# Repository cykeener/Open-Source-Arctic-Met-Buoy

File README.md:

# Open-Source-Arctic-Met-Buoy
General info, PCB design files, and hull / enclosure design files to build a meteorological (met) buoy to collect GPS location, external temperature, and atmospheric pressure in a cold weather environment.  This version of the buoy was designed in the fall of 2018, and deployed in the winter of 2019.

The intent of this repository is to maintain general info, PCB design files (from Eagle), 3D printable stl files (from Fusion 360), and a series of BOMs that will allow the user to build an open source met buoy that runs on Arduino code maintained by tgidave https://github.com/tgidave/icedrifter

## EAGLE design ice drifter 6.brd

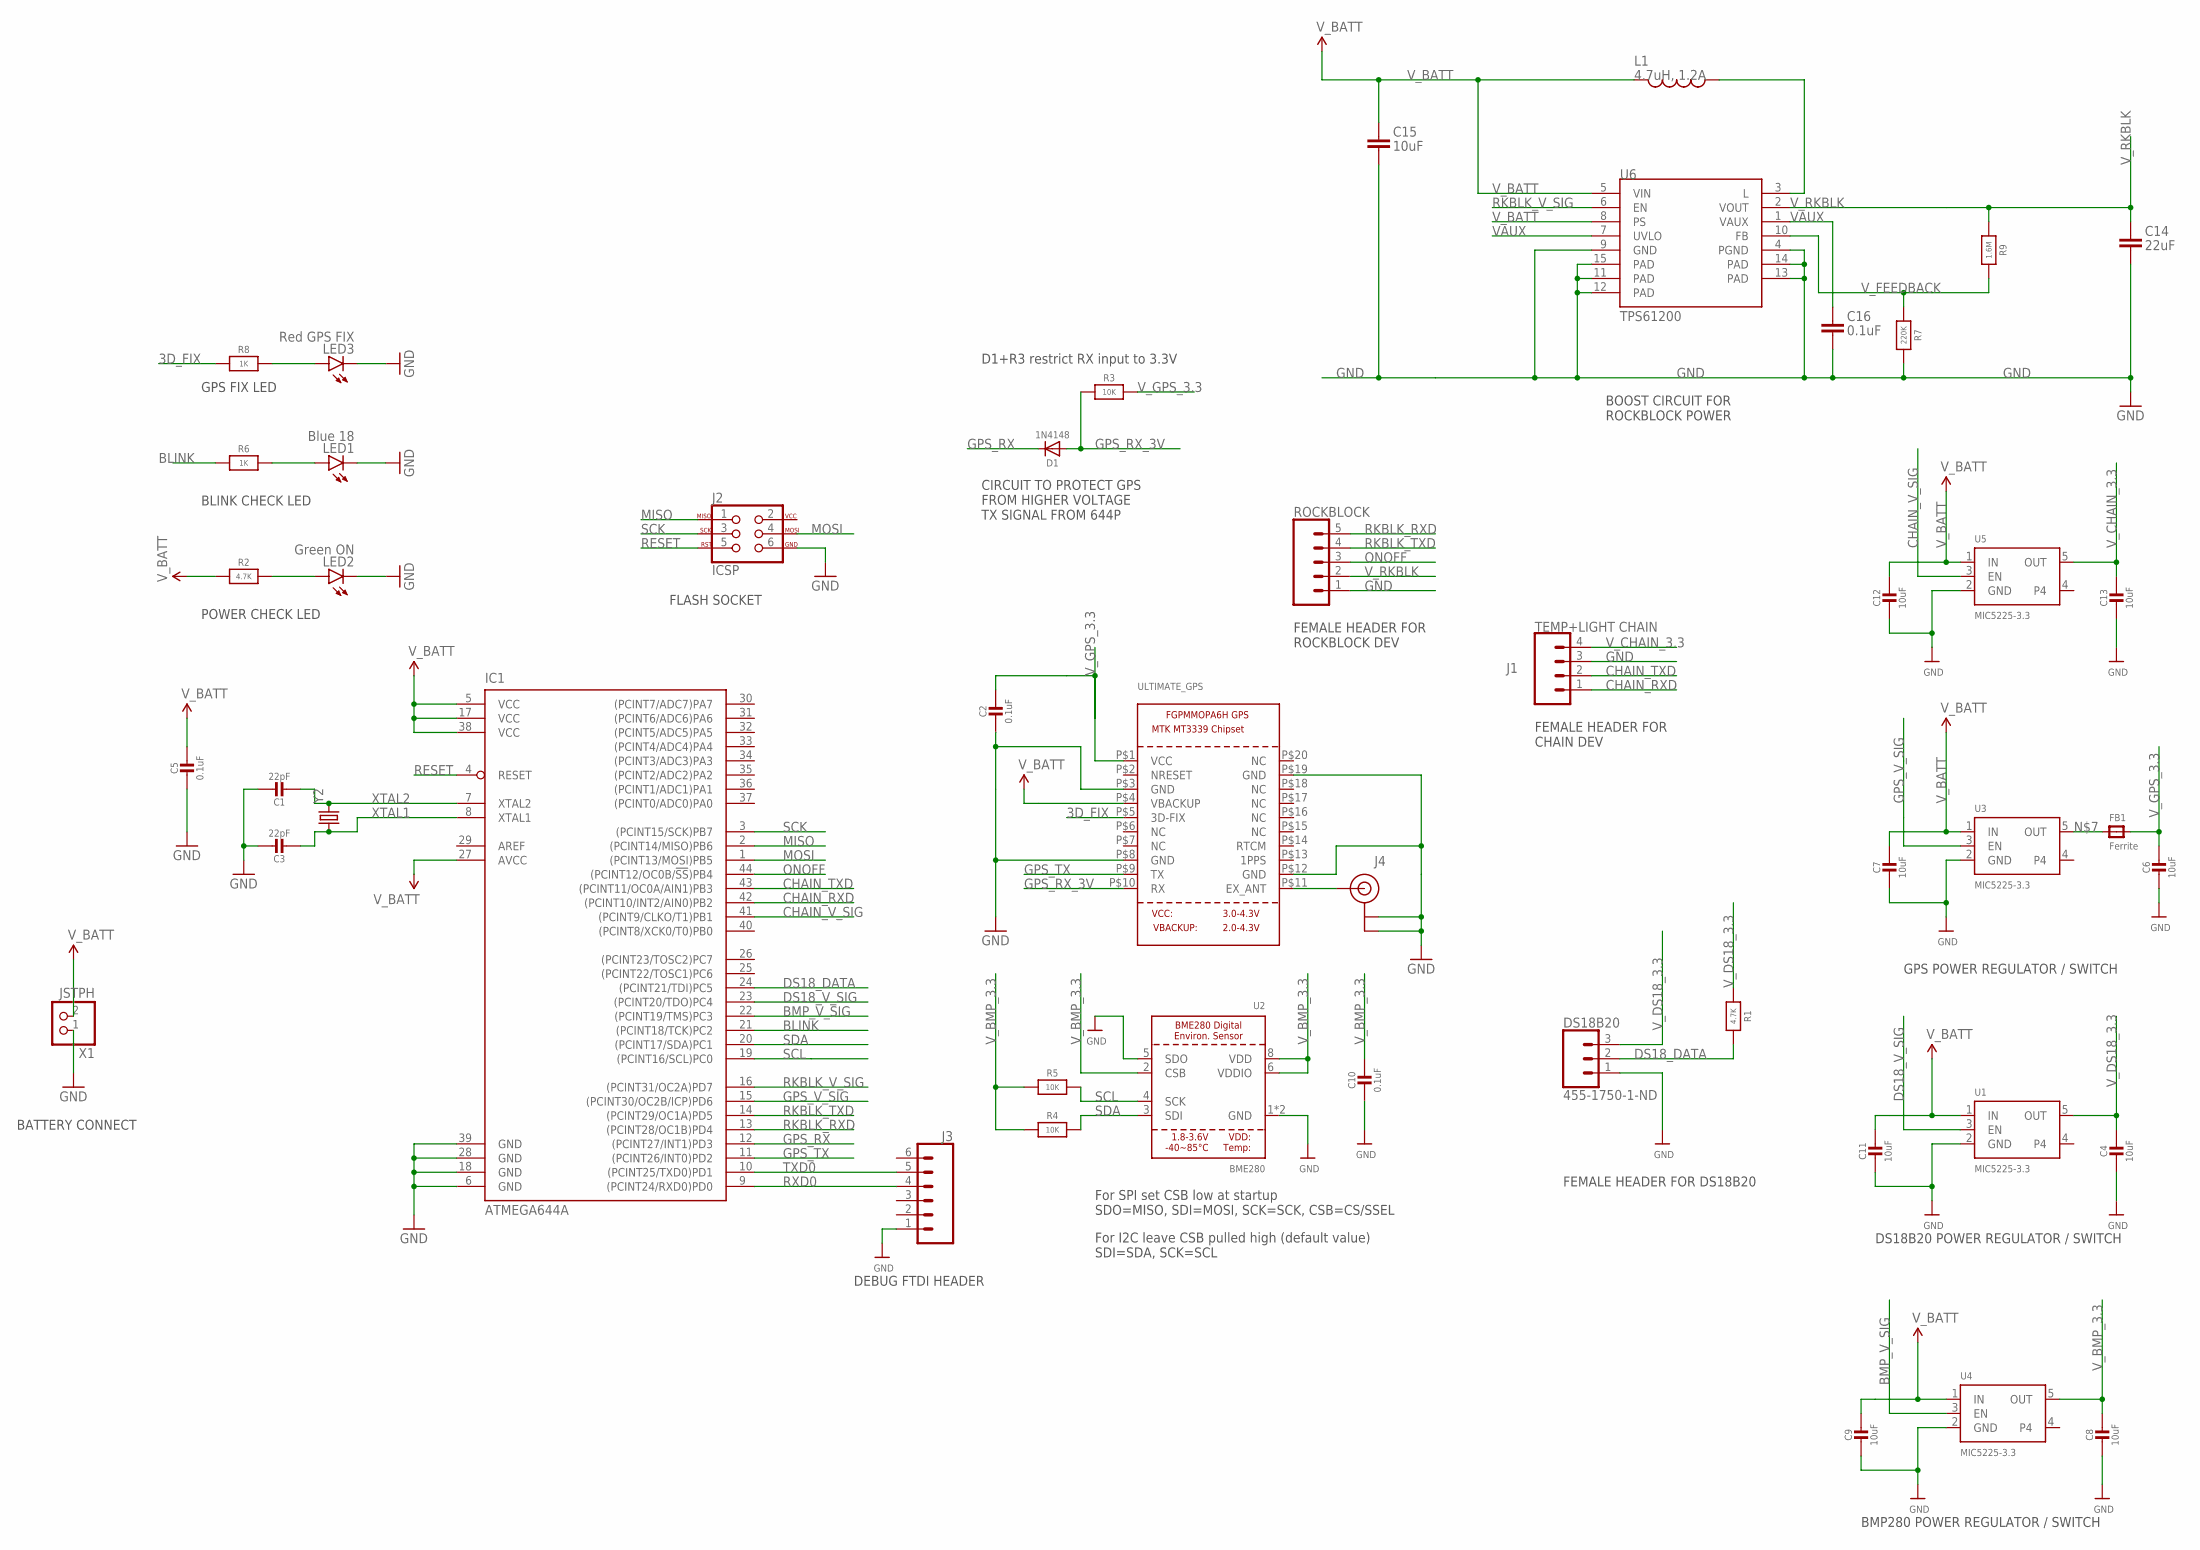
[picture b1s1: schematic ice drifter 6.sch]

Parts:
C1, C3: 22pF; 0805-NO@2
C2, C5, C10: 0.1uF; 0805-NO@2
C4, C6, C7, C8, C9, C11, C12, C13: 10uF; 0805-NO@2
C14: 22uF; 0805
C15: 10uF; 1206
C16: 0.1uF; 0805
D1: 1N4148; SOD-323
DS18B20: 455-1750-1-ND; 1X03
FB1: Ferrite; 0805-NO@1
IC1: ATMEGA644A; TQFP44
J1: TEMP+LIGHT CHAIN; 1X04
J2: ICSP; 2X3-NS
J3: CONN_06SILK_FEMALE_PTH; 1X06
J4: U.FL
L1: 4.7uH, 1.2A; CDRH2D09
LED1: Blue 18; LED-1206
LED2: Green ON; LED-1206
LED3: Red GPS FIX; LED-1206
R1, R2: 4.7K; 0805-NO
R3, R4, R5: 10K; 0805-NO
R6, R8: 1K; 0805-NO
R7: 220K; 0805-NO
R9: 1.6M; 0805-NO
ROCKBLOCK: CONN_05; 1X05
U1, U3, U4, U5: MIC5225-3.3; SOT23-5
U2: BME280
U6: TPS61200; QFN-10_PAD
ULTIMATE_GPS: GPS_FGPMMOPA6H; FGPMMOPA6H
X1: JSTPH; JSTPH2
Y2: CRYSTALTXC-7A; CRYSTAL-TXC-7A

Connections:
3D_FIX: R8.1, ULTIMATE_GPS.P$5 (3D-FIX)
BLINK: IC1.21 ((PCINT18/TCK)PC2), R6.1
BMP_V_SIG: IC1.22 ((PCINT19/TMS)PC3), U4.3 (EN)
CHAIN_RXD: IC1.42 ((PCINT10/INT2/AIN0)PB2), J1.1
CHAIN_TXD: IC1.43 ((PCINT11/OC0A/AIN1)PB3), J1.2
CHAIN_V_SIG: IC1.41 ((PCINT9/CLKO/T1)PB1), U5.3 (EN)
COIL: L1.P$1 (1), U6.3 (L)
DS18_DATA: DS18B20.2, IC1.24 ((PCINT21/TDI)PC5), R1.2
DS18_V_SIG: IC1.23 ((PCINT20/TDO)PC4), U1.3 (EN)
GND: C1.1, C2.2, C3.1, C4.2, C5.2, C6.2, C7.2, C8.2, C9.2, C10.2, C11.2, C12.2, C13.2, C14.2, C15.2, C16.2, DS18B20.1, IC1.6 (GND), IC1.18 (GND), IC1.28 (GND), IC1.39 (GND), J1.3, J2.6, J3.1, J4.1 (GND), J4.2 (GND), LED1.C, LED2.C, LED3.C, R7.2, ROCKBLOCK.1, U1.2 (GND), U2.1 (GND), U2.5 (SDO), U2.7 (GND), U3.2 (GND), U4.2 (GND), U5.2 (GND), U6.4 (PGND), U6.9 (GND), U6.11 (PAD), U6.12 (PAD), U6.13 (PAD), U6.14 (PAD), U6.15 (PAD), ULTIMATE_GPS.P$3 (GND), ULTIMATE_GPS.P$8 (GND), ULTIMATE_GPS.P$12 (GND), ULTIMATE_GPS.P$19 (GND), X1.1
GPS_RX: D1.C, IC1.12 ((PCINT27/INT1)PD3)
GPS_RX_3V: D1.A, R3.1, ULTIMATE_GPS.P$10 (RX)
GPS_TX: IC1.11 ((PCINT26/INT0)PD2), ULTIMATE_GPS.P$9 (TX)
GPS_V_SIG: IC1.15 ((PCINT30/OC2B/ICP)PD6), U3.3 (EN)
MISO: IC1.2 ((PCINT14/MISO)PB6), J2.1
MOSI: IC1.1 ((PCINT13/MOSI)PB5), J2.4
unnamed: LED2.A, R2.2
unnamed: LED1.A, R6.2
unnamed: LED3.A, R8.2
unnamed: FB1.1, U3.5 (OUT)
ONOFF: IC1.44 ((PCINT12/OC0B/!SS!)PB4), ROCKBLOCK.3
RESET: IC1.4 (RESET), J2.5
RKBLK_RXD: IC1.13 ((PCINT28/OC1B)PD4), ROCKBLOCK.5
RKBLK_TXD: IC1.14 ((PCINT29/OC1A)PD5), ROCKBLOCK.4
RKBLK_V_SIG: IC1.16 ((PCINT31/OC2A)PD7), U6.6 (EN)
RXD0: IC1.9 ((PCINT24/RXD0)PD0), J3.4
SCK: IC1.3 ((PCINT15/SCK)PB7), J2.3
SCL: IC1.19 ((PCINT16/SCL)PC0), R5.2, U2.4 (SCK)
SDA: IC1.20 ((PCINT17/SDA)PC1), R4.2, U2.3 (SDI)
TXD0: IC1.10 ((PCINT25/TXD0)PD1), J3.5
U.FL_ANT: J4.FEED (SIGNAL), ULTIMATE_GPS.P$11 (EX_ANT)
VAUX: C16.1, U6.1 (VAUX), U6.7 (UVLO)
V_BATT: C5.1, C7.1, C9.1, C11.1, C12.1, C15.1, IC1.5 (VCC), IC1.17 (VCC), IC1.27 (AVCC), IC1.38 (VCC), L1.P$2 (2), R2.1, U1.1 (IN), U3.1 (IN), U4.1 (IN), U5.1 (IN), U6.5 (VIN), U6.8 (PS), ULTIMATE_GPS.P$4 (VBACKUP), X1.2
V_BMP_3.3: C8.1, C10.1, R4.1, R5.1, U2.2 (CSB), U2.6 (VDDIO), U2.8 (VDD), U4.5 (OUT)
V_CHAIN_3.3: C13.1, J1.4, U5.5 (OUT)
V_DS18_3.3: C4.1, DS18B20.3, R1.1, U1.5 (OUT)
V_FEEDBACK: R7.1, R9.2, U6.10 (FB)
V_GPS_3.3: C2.1, C6.1, FB1.2, R3.2, ULTIMATE_GPS.P$1 (VCC)
V_RKBLK: C14.1, R9.1, ROCKBLOCK.2, U6.2 (VOUT)
XTAL1: C3.2, IC1.8 (XTAL1), Y2.P$1 (1)
XTAL2: C1.2, IC1.7 (XTAL2), Y2.P$2 (2)

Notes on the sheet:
For SPI set CSB low at startup SDO=MISO, SDI=MOSI, SCK=SCK, CSB=CS/SSEL
For I2C leave CSB pulled high (default value) SDI=SDA, SCK=SCL
D1+R3 restrict RX input to 3.3V
GPS POWER REGULATOR / SWITCH
DS18B20 POWER REGULATOR / SWITCH
BMP280 POWER REGULATOR / SWITCH
FEMALE HEADER FOR DS18B20
DEBUG FTDI HEADER
FEMALE HEADER FOR ROCKBLOCK DEV
BOOST CIRCUIT FOR ROCKBLOCK POWER
CIRCUIT TO PROTECT GPS FROM HIGHER VOLTAGE TX SIGNAL FROM 644P
BATTERY CONNECT
POWER CHECK LED
BLINK CHECK LED
GPS FIX LED
FLASH SOCKET
FEMALE HEADER FOR CHAIN DEV

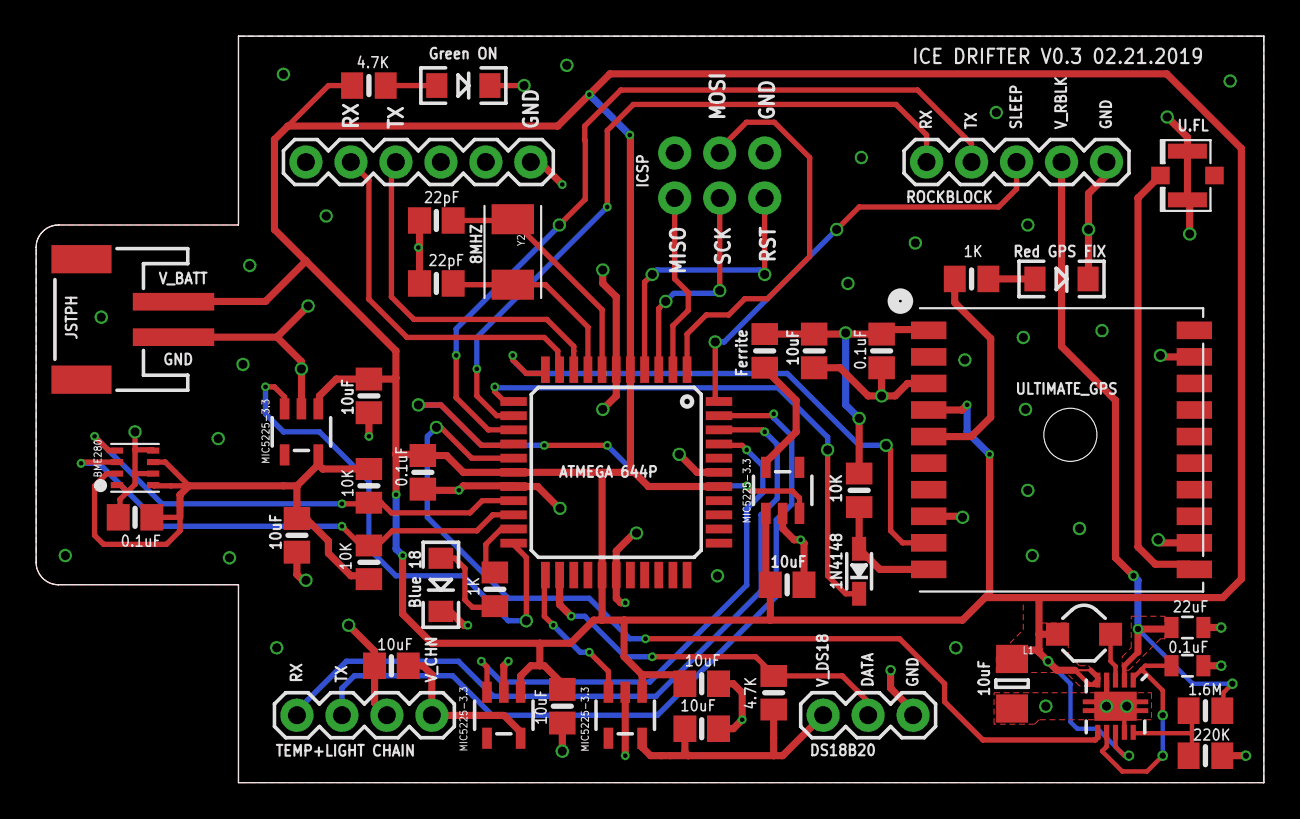
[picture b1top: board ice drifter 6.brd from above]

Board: 2 copper layers, 69.3 x 42.2 mm, 47 parts (0 on the bottom side), 41 nets.

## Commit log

2019-09-24 PCB Version 6
    Use with Arduino code: https://github.com/tgidave/icedrifter
2019-09-24 stl print files for the buoy hull
    There is a top file, bottom file, and PCB tray to fit Icedrifter 6 PCB, and a Rockblock 9602 modem. Look to the readme for info on fasteners and o-rings from McMaster-Carr.

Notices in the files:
parts and their libraries:
SparkFun-Connectors: Licensing: Creative Commons ShareAlike 4.0 International - https://creativecommons.org/licenses/by-sa/4.0
SparkFun-LED: Licensing: CC v3.0 Share-Alike You are welcome to use this library for commercial purposes.
